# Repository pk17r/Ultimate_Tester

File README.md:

# Ultimate Tester!

Pocket Sized Component Tester + Variable Power Source + Accurate Power Monitor in Arduino Uno Form Factor

Full Blog Entry & Details:
https://pk17r.wordpress.com/2023/12/18/ultimate-tester-component-tester-lipo-charge-boost-protect/

Updated Ultimate Tester Schematics: https://github.com/pk17r/Ultimate_Tester/blob/prash/ComponentTester-1.54m/UltimateTester_PCB/UltimateTester_v1_with_mods.pdf

<br>

Current Accuracy:<br>
Test 1: Low Current: 2.4mA<br>
<table>
  <tr>
    <th></th>
    <th>Measured</th>
    <th>Ground Truth</th>
    <th>Error</th>
  </tr>
  <tr>
    <td>Current</td>
    <td>2.4mA</td>
    <td>2.39+0.6%=2.40mA</td>
    <td>0%</td>
  </tr>
  <tr>
    <td>Voltage</td>
    <td>5.17V</td>
    <td>5.164+0.1%=5.17V</td>
    <td>0%</td>
  </tr>
</table>

Test 2: Medium Current: 209.3mA<br>
<table>
  <tr>
    <th></th>
    <th>Measured</th>
    <th>Ground Truth</th>
    <th>Error</th>
  </tr>
  <tr>
    <td>Current</td>
    <td>209.3mA</td>
    <td>207.3+0.6%=208.5mA</td>
    <td>+0.4%</td>
  </tr>
  <tr>
    <td>Voltage</td>
    <td>5.14V</td>
    <td>5.135+0.1%=5.14V</td>
    <td>0%</td>
  </tr>
</table>

Test 3: High Current: 1.07A<br>
<table>
  <tr>
    <th></th>
    <th>Measured</th>
    <th>Ground Truth</th>
    <th>Error</th>
  </tr>
  <tr><td>Current</td><td>1.07mA</td><td>1.056+0.6%=1.06A</td><td>+0.9%</td></tr>
  <tr><td>Voltage</td><td>4.95V </td><td>4.928+0.1%=4.93V</td><td>+0.4%</td></tr>
</table>

Test 4: Different Voltages<br>
<table>
  <tr>
    <th>Measured</th>
    <th>Ground Truth</th>
    <th>Error</th>
  </tr>
  <tr><td>3.93V</td><td>  3.930+0.1%=3.93V</td><td>    0%</td></tr>
  <tr><td>9.05V</td><td>  9.051+0.1%=9.02V</td><td>   +0.3%</td></tr>
  <tr><td>12.04V</td><td>12.022+0.1%=12.03V</td><td>+0.1%</td></tr>
  <tr><td>15.15V</td><td>15.136+0.1%=15.15V</td><td>0%</td></tr>
</table>

<br>

# Transistortester Warehouse

The Transistortester is a device for identifying and checking electronic components.
It also offers additional functionality like a PWM signal generator for example.
And it's OSHW.

This repo is meant to provide a convenient way to download firmware packages,
documentation files, PCB files and more. Therefore it's structured differently
from the main repo.

The project's webpage is https://www.mikrocontroller.net/articles/AVR_Transistortester
and the main repo is https://github.com/kubi48/TransistorTester-source.

BTW, all the inexpensive Transistortesters sold on your favourite shopping platform
are based on this project and can be updated with the original OSHW firmware versions.

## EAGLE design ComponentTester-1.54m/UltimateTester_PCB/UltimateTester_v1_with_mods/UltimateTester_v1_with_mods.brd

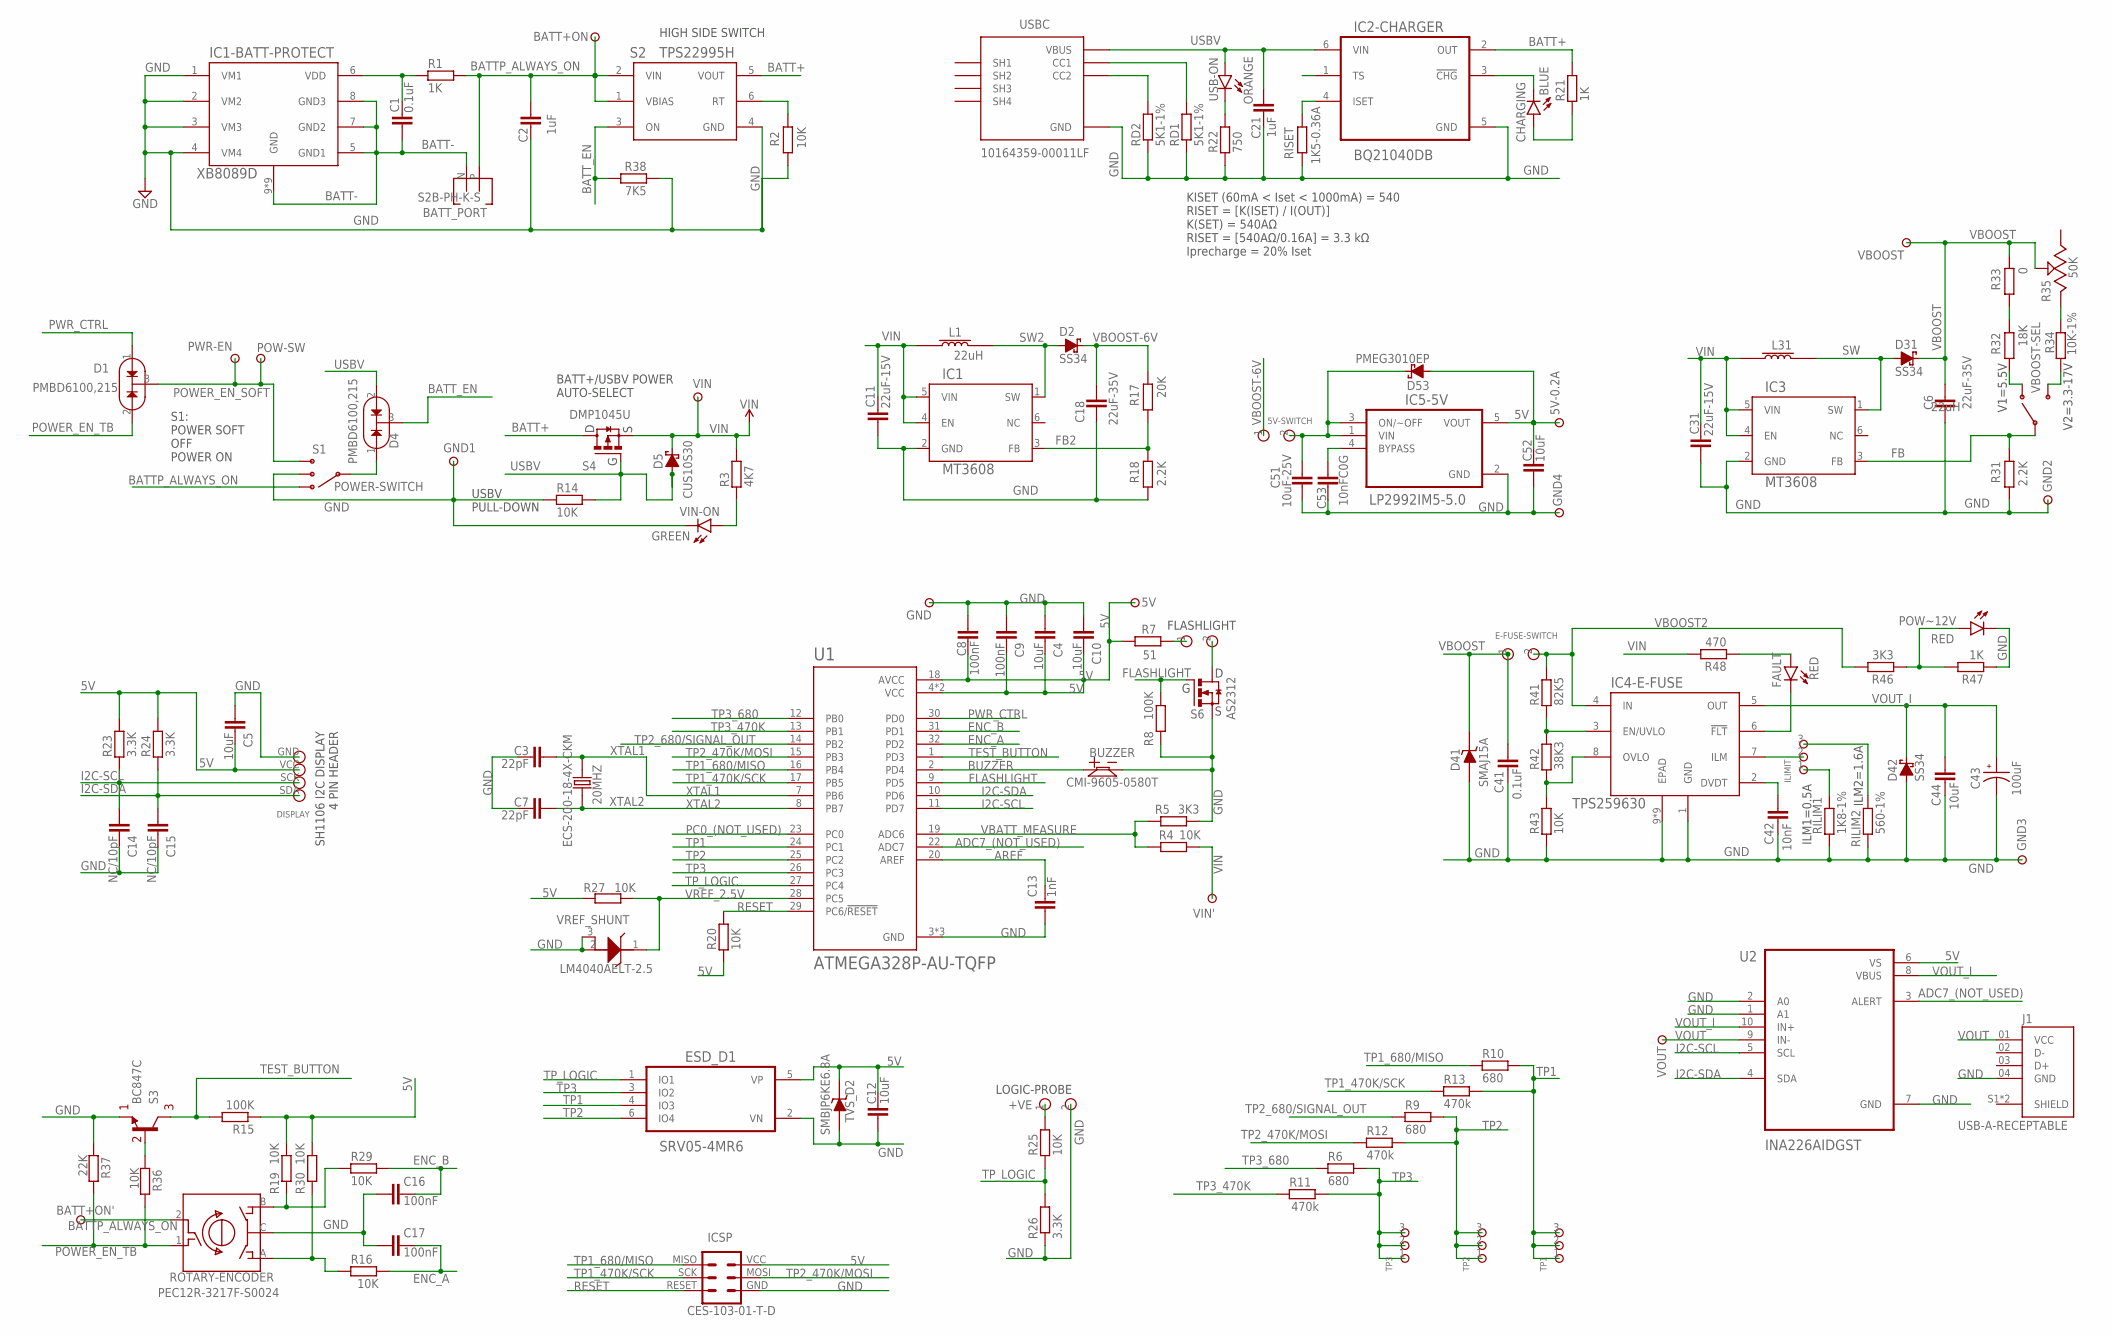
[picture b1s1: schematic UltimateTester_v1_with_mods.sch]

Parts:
5V, 5V-0.2A: TEST-POINT-TH; TEST-POINT-TH-1MM
5V-SWITCH: HEADER-2PIN-0.1"P
20MHZ: ECS-200-18-4X-CKM; XTAL_ECS-200-18-4X-CKM
BATT+ON: TEST-POINT-TH; TEST-POINT-TH-1MM
BATT+ON': TEST-POINT-TH; TEST-POINT-TH-1MM
BATT_PORT: S2B-PH-K-S
BUZZER: CMI-9605-0580T; BUZZER-ACTIVE-CMI-9605-0580T
C1, C41: 0.1uF; 0603
C2, C21: 1uF; 0603
C3, C7: 22pF; 0603
C4, C10, C12, C44, C52: 10uF; 0603
C5: 10uF; 1206
C6, C18: 22uF-35V; 1206
C8, C9, C16, C17: 100nF; 0603
C11, C31: 22uF-15V; 1206
C13: 1nF; 0603
C14, C15: NC/10pF; 0603
C42: 10nF; 0603
C43: 100uF; CAP_EEEFN1E101UP
C51: 10uF-25V; 0603
C53: 10nFC0G; 0603
CHARGING: BLUE; 0603-DIODE
D1, D4: PMBD6100,215; SOT-23-3
D2, D31, D42: SS34; SMA
D5: CUS10S30; SOD-323
D41: SMAJ15A; SMA
D53: PMEG3010EP; SOD-128
DISPLAY: DISPLAY-1.3"-SH1106-I2C
E-FUSE-SWITCH: HEADER-2PIN-0.1"P
ESD_D1: SRV05-4MR6; SOT-23-6
FAULT: RED; 0603-DIODE
FLASHLIGHT: HEADER-2PIN-0.2"P
GND, GND1, GND2, GND3, GND4: TEST-POINT-TH; TEST-POINT-TH-1MM
IC1, IC3: MT3608; SOT-23-6
IC1-BATT-PROTECT: XB8089D; SOIC-8-POWER-PAD
IC2-CHARGER: BQ21040DB; SOT-23-6
IC4-E-FUSE: TPS259630; SOIC-8-POWER-PAD
IC5-5V: LP2992IM5-5.0; SOT-23-5
ICSP: CES-103-01-T-D; HEADER-ICSP-0.1"P
ILIMIT: HEADER-3PIN-0.1"P
J1: USB-A-RECEPTABLE; AMPHENOL_87583-2010RLF
L1, L31: 22uH; INDUCTOR-SMRH74-220MT
LOGIC-PROBE: HEADER-2PIN-0.1"P
POW-SW: TEST-POINT-TH; TEST-POINT-TH-1MM
POW~12V: RED; 1206-DIODE
PWR-EN: TEST-POINT-TH; TEST-POINT-TH-1MM
R1, R21, R47: 1K; 0603
R2, R4, R14, R16, R19, R20, R25, R27, R29, R30, R36, R43: 10K; 0603
R3: 4K7; 0603
R5, R46: 3K3; 0603
R6, R9, R10: 680; 1206
R7: 51; 1206
R8, R15: 100K; 0603
R11, R12, R13: 470k; 1206
R17: 20K; 0603
R18, R31: 2.2K; 0603
R22: 750; 0603
R23, R24, R26: 3.3K; 0603
R32: 18K; 0603
R33: 0; 0603
R34: 10K-1%; 0603
R35: 50K; ROTARY-POTENTIOMETER-3386P
R37: 22K; 0603
R38: 7K5; 0603
R41: 82K5; 0603
R42: 38K3; 0603
R48: 470; 0603
RD1, RD2: 5K1-1%; 0603
RILIM1: 1K8-1%; 0603
RILIM2: 560-1%; 0603
RISET: 1K5-0.36A; 0603
ROTARY-ENCODER: PEC12R-3217F-S0024
S1: POWER-SWITCH; CSS-1310MC
S2: TPS22995H; SOT-23-6
S3: BC847C; SOT-23-3
S4: DMP1045U; SOT-23-3
S6: AS2312; SOT-23-3
TP1, TP2, TP3: HEADER-3PIN-0.1"P
TVS_D2: SMBJP6KE6.8A; DIOM5336X244N
U1: ATMEGA328P-AU-TQFP; TQFP32
U2: INA226AIDGST; SOP50P490X110-10N
USB-ON: ORANGE; 0603-DIODE
USBC: 10164359-00011LF; USB-C-RECEPTABLE-1016435900011LF
VBOOST: TEST-POINT-TH; TEST-POINT-TH-1MM
VBOOST-SEL: SLIDE-SWITCH-SPDT-VERTICLE-TH; SLW-883935-2A-D
VIN: TEST-POINT-TH; TEST-POINT-TH-1MM
VIN': TEST-POINT-TH; TEST-POINT-TH-1MM
VIN-ON: GREEN; 0603-DIODE
VOUT: TEST-POINT-TH; TEST-POINT-TH-1MM
VREF_SHUNT: LM4040AELT-2.5; SOT-23-3

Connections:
5V: 5V.P$1, 5V-0.2A.P$1, C4.1, C5.1, C8.2, C9.1, C10.1, C12.1, C52.2, D53.A, DISPLAY.VCC, ESD_D1.5 (VP), IC5-5V.5 (VOUT), ICSP.VCC (2), R7.1, R15.1, R19.2, R20.1, R23.2, R24.2, R27.1, R30.2, TVS_D2.C, U1.4 (VCC), U1.6 (VCC), U1.18 (AVCC), U2.6 (VS)
!FLT: FAULT.C, IC4-E-FUSE.6 (!FLT)
+VE: LOGIC-PROBE.1, R25.2
A: R16.1, R30.1, ROTARY-ENCODER.A
ADC7_(NOT_USED): U1.22 (ADC7), U2.3 (ALERT)
AREF: C13.1, U1.20 (AREF)
B: R19.1, R29.1, ROTARY-ENCODER.B
BATT+: IC2-CHARGER.2 (OUT), R21.2, S2.5 (VOUT), S4.3 (D)
BATT-: BATT_PORT.N, C1.2, IC1-BATT-PROTECT.5 (GND1), IC1-BATT-PROTECT.7 (GND2), IC1-BATT-PROTECT.8 (GND3), IC1-BATT-PROTECT.9 (GND), IC1-BATT-PROTECT.10 (GND), IC1-BATT-PROTECT.11 (GND), IC1-BATT-PROTECT.12 (GND), IC1-BATT-PROTECT.13 (GND), IC1-BATT-PROTECT.14 (GND), IC1-BATT-PROTECT.15 (GND), IC1-BATT-PROTECT.16 (GND), IC1-BATT-PROTECT.17 (GND)
BATTP_ALWAYS_ON: BATT+ON.P$1, BATT+ON'.P$1, BATT_PORT.P, C2.2, R1.2, ROTARY-ENCODER.2, S1.1, S2.1 (VBIAS), S2.2 (VIN)
BATT_EN: D4.3 (C), R38.2, S2.3 (ON)
BJT-B: R36.1, S3.1 (B)
BUZZER: BUZZER.P$1 (+), U1.2 (PD4)
BYP1: C53.2, IC5-5V.4 (BYPASS)
CHG: CHARGING.C, IC2-CHARGER.3 (!CHG)
DVDT: C42.2, IC4-E-FUSE.2 (DVDT)
EN/UVLO: IC4-E-FUSE.3 (EN/UVLO), R41.1, R42.2
ENC_A: C17.1, R16.2, U1.32 (PD2)
ENC_B: C16.1, R29.2, U1.31 (PD1)
FB: IC3.3 (FB), R31.1, VBOOST-SEL.C
FB2: IC1.3 (FB), R17.2, R18.1
FL+: FLASHLIGHT.1, R7.2
FL-: FLASHLIGHT.2, S6.3 (D)
FLASHLIGHT: R8.1, S6.1 (G), U1.9 (PD5)
GND: BUZZER.P$2 (-), C2.1, C3.1, C4.2, C5.2, C6.1, C7.1, C8.1, C9.2, C10.2, C11.1, C12.2, C13.2, C14.1, C15.1, C16.2, C17.2, C18.1, C21.1, C31.1, C41.1, C42.1, C43.2, C44.1, C51.1, C52.1, C53.1, D41.A, D42.A, DISPLAY.GND, ESD_D1.2 (VN), GND.P$1, GND1.P$1, GND2.P$1, GND3.P$1, GND4.P$1, IC1.2 (GND), IC1-BATT-PROTECT.1 (VM1), IC1-BATT-PROTECT.2 (VM2), IC1-BATT-PROTECT.3 (VM3), IC1-BATT-PROTECT.4 (VM4), IC2-CHARGER.5 (GND), IC3.2 (GND), IC4-E-FUSE.1 (GND), IC4-E-FUSE.9 (EPAD), IC4-E-FUSE.10 (EPAD), IC4-E-FUSE.11 (EPAD), IC4-E-FUSE.12 (EPAD), IC4-E-FUSE.13 (EPAD), IC4-E-FUSE.14 (EPAD), IC4-E-FUSE.15 (EPAD), IC4-E-FUSE.16 (EPAD), IC4-E-FUSE.17 (EPAD), IC5-5V.2 (GND), ICSP.GND (6), J1.04 (GND), LOGIC-PROBE.2, POW~12V.C1 (C), R2.2, R5.2, R8.2, R14.1, R18.2, R22.1, R26.1, R31.2, R37.1, R38.1, R43.1, R47.1, RD1.1, RD2.1, RILIM1.1, RILIM2.1, RISET.2, ROTARY-ENCODER.C, S1.2, S2.4 (GND), S3.2 (E), S6.2 (S), TVS_D2.A, U1.3 (GND), U1.5 (GND), U1.21 (GND), U2.1 (A1), U2.2 (A0), U2.7 (GND), USBC.A12 (GND), USBC.B12 (GND), VIN-ON.C, VREF_SHUNT.2 (A), VREF_SHUNT.3 (NC/A)
I2C-SCL: C14.2, DISPLAY.SCK, R23.1, U1.11 (PD7), U2.5 (SCL)
I2C-SDA: C15.2, DISPLAY.SDA, R24.1, U1.10 (PD6), U2.4 (SDA)
ILM: IC4-E-FUSE.7 (ILM), ILIMIT.2
ILM1: ILIMIT.1, RILIM1.2
ILM2: ILIMIT.3, RILIM2.2
ISET: IC2-CHARGER.4 (ISET), RISET.1
unnamed: RD2.2, USBC.B5 (CC2)
unnamed: RD1.2, USBC.A5 (CC1)
unnamed: R22.2, USB-ON.C
unnamed: R32.2, VBOOST-SEL.1
unnamed: R3.1, VIN-ON.A
unnamed: FAULT.A, R48.1
unnamed: CHARGING.A, R21.1
unnamed: R32.1, R33.2
unnamed: R34.2, VBOOST-SEL.2
unnamed: POW~12V.A1 (A), R46.1, R47.2
unnamed: R34.1, R35.3 (CCW)
OVLO: IC4-E-FUSE.8 (OVLO), R42.1, R43.2
PC0_(NOT_USED): U1.23 (PC0)
POWER_EN_SOFT: D1.3 (C), POW-SW.P$1, PWR-EN.P$1, S1.3
POWER_EN_TB: D1.2 (A2), R36.2, R37.2, ROTARY-ENCODER.1
PWR_CTRL: D1.1 (A1), U1.30 (PD0)
PWR_SW: D4.1 (A1), S1.C
RESET: ICSP.RESET (5), R20.2, U1.29 (PC6/!RESET)
RT: R2.1, S2.6 (RT)
SW: D31.A, IC3.1 (SW), L31.P$2
SW2: D2.A, IC1.1 (SW), L1.P$2
TEST_BUTTON: R15.2, S3.3 (C), U1.1 (PD3)
TP1: ESD_D1.4 (IO3), R10.2, R13.2, TP1.1, TP1.2, TP1.3, U1.24 (PC1)
TP1_470K/SCK: ICSP.SCK (3), R13.1, U1.17 (PB5)
TP1_680/MISO: ICSP.MISO (1), R10.1, U1.16 (PB4)
TP2: ESD_D1.6 (IO4), R9.2, R12.2, TP2.1, TP2.2, TP2.3, U1.25 (PC2)
TP2_470K/MOSI: ICSP.MOSI (4), R12.1, U1.15 (PB3)
TP2_680/SIGNAL_OUT: R9.1, U1.14 (PB2)
TP3: ESD_D1.3 (IO2), R6.2, R11.2, TP3.1, TP3.2, TP3.3, U1.26 (PC3)
TP3_470K: R11.1, U1.13 (PB1)
TP3_680: R6.1, U1.12 (PB0)
TP_LOGIC: ESD_D1.1 (IO1), R25.1, R26.2, U1.27 (PC4)
TS: IC2-CHARGER.1 (TS)
USBV: C21.2, D4.2 (A2), D5.A, IC2-CHARGER.6 (VIN), R14.2, S4.1 (G), USB-ON.A, USBC.A9 (VBUS), USBC.B9 (VBUS)
VBATT_MEASURE: R4.2, R5.1, U1.19 (ADC6)
VBOOST: C6.2, C41.2, D31.C, D41.C, E-FUSE-SWITCH.1, R33.1, R35.2 (S), VBOOST.P$1
VBOOST2: E-FUSE-SWITCH.2, IC4-E-FUSE.4 (IN), R41.2, R46.2
VBOOST-6V: 5V-SWITCH.1, C18.2, D2.C, R17.1
VBOOST-6V-: 5V-SWITCH.2, C51.2, D53.K (C), IC5-5V.1 (VIN), IC5-5V.3 (ON/~OFF)
VDD: C1.1, IC1-BATT-PROTECT.6 (VDD), R1.1
VIN: C11.2, C31.2, D5.C, IC1.4 (EN), IC1.5 (VIN), IC3.4 (EN), IC3.5 (VIN), L1.P$1, L31.P$1, R3.2, R4.1, R48.2, S4.2 (S), VIN.P$1, VIN'.P$1
VOUT: J1.01 (VCC), U2.9 (IN-), VOUT.P$1
VOUT_I: C43.1, C44.2, D42.C, IC4-E-FUSE.5 (OUT), U2.8 (VBUS), U2.10 (IN+)
VREF_2.5V: R27.2, U1.28 (PC5), VREF_SHUNT.1 (C)
XTAL1: 20MHZ.2, C3.2, U1.7 (PB6)
XTAL2: 20MHZ.1, C7.2, U1.8 (PB7)

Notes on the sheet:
HIGH SIDE SWITCH
KISET (60mA < Iset < 1000mA) = 540 RISET = [K(ISET) / I(OUT)] K(SET) = 540AΩ RISET = [540AΩ/0.16A] = 3.3 kΩ Iprecharge = 20% Iset
BATT+/USBV POWER AUTO-SELECT
USBV PULL-DOWN
S1: POWER SOFT OFF POWER ON
V1=5.5V
V2=3.3-17V
ILM2=1.6A
ILM1=0.5A

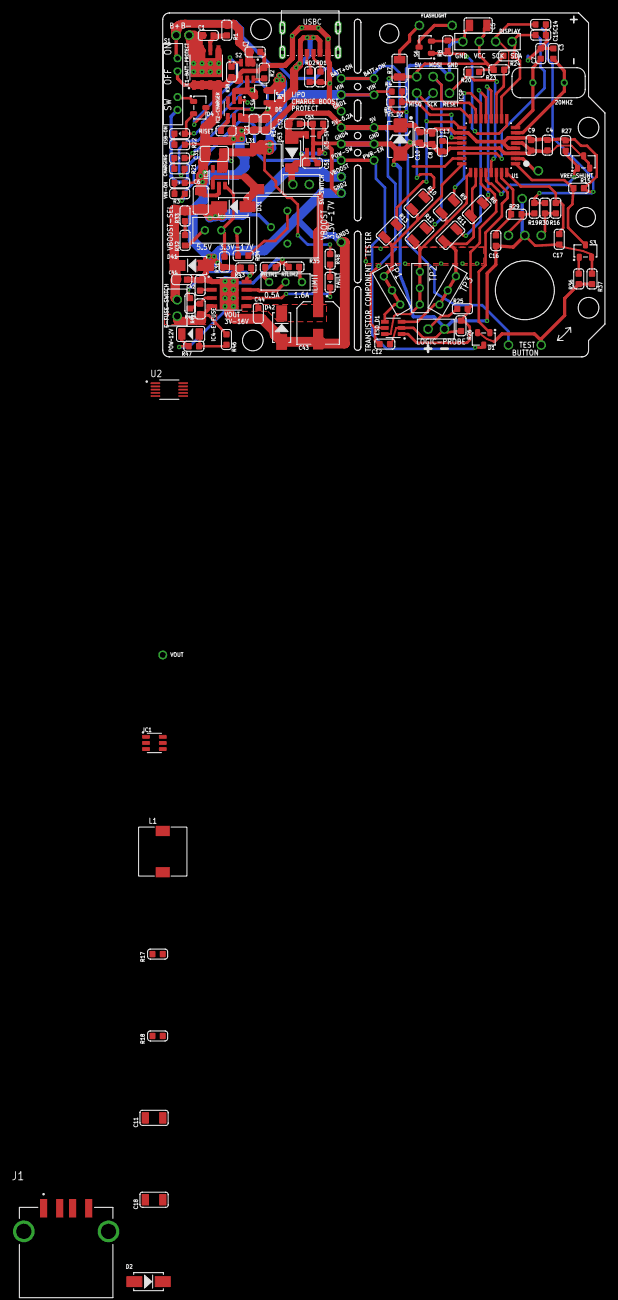
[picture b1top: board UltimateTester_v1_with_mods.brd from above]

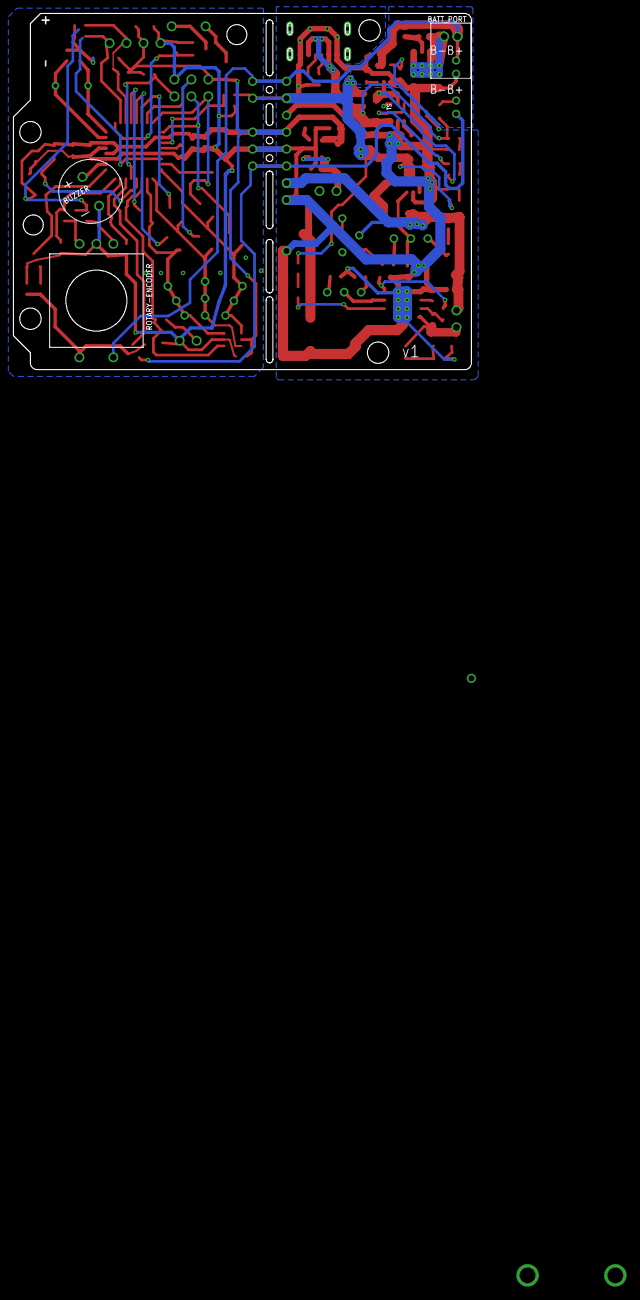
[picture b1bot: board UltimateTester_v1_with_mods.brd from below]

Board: 2 copper layers, 68.6 x 53.3 mm, 138 parts (2 on the bottom side), 75 nets.

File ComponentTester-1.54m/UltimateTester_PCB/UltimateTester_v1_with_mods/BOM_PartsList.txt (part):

Partlist

Exported from LiBatteryChargeBoostBoard.sch at 17-Dec-23 11:04 PM

EAGLE Version 9.6.2 Copyright (c) 1988-2020 Autodesk, Inc.

Assembly variant: 

Part             Value              Device                                   Package                          Library       Sheet

5V               TEST-POINT-TH      TEST-POINT-TH                            TEST-POINT-TH-1MM                .MyComponents 1
5V-0.2A          TEST-POINT-TH      TEST-POINT-TH                            TEST-POINT-TH-1MM                .MyComponents 1
5V-SWITCH                           HEADER-2PIN-0.1"P                        HEADER-2PIN-0.1"P                .MyComponents 1
20MHZ            ECS-200-18-4X-CKM  CRYSTAL-20MHZ-ECS-200-18-4X-CKM          XTAL_ECS-200-18-4X-CKM           .MyComponents 1
BATT+ON          TEST-POINT-TH      TEST-POINT-TH                            TEST-POINT-TH-1MM                .MyComponents 1
BATT+ON'         TEST-POINT-TH      TEST-POINT-TH                            TEST-POINT-TH-1MM                .MyComponents 1
BATT_PORT        S2B-PH-K-S         S2B-PH-K-S                               S2B-PH-K-S                       .MyComponents 1
BUZZER           CMI-9605-0580T     BUZZER-ACTIVE-CMI-9605-0580T             BUZZER-ACTIVE-CMI-9605-0580T     .MyComponents 1
C1               0.1uF              CAPACITOR_SMD0603                        0603                             .MyComponents 1
C2               1uF                CAPACITOR_SMD0603                        0603                             .MyComponents 1
C3               22pF               CAPACITOR_SMD0603                        0603                             .MyComponents 1
C4               10uF               CAPACITOR_SMD0603                        0603                             .MyComponents 1
C5               10uF               CAPACITOR1206                            1206                             .MyComponents 1
C6               22uF-35V           CAPACITOR_SMD1206                        1206                             .MyComponents 1
C7               22pF               CAPACITOR_SMD0603                        0603                             .MyComponents 1
C8               100nF              CAPACITOR_SMD0603                        0603                             .MyComponents 1
C9               100nF              CAPACITOR_SMD0603                        0603                             .MyComponents 1
C10              10uF               CAPACITOR_SMD0603                        0603                             .MyComponents 1
C12              10uF               CAPACITOR_SMD0603                        0603                             .MyComponents 1
C13              1nF                CAPACITOR_SMD0603                        0603                             .MyComponents 1
C14              NC/10pF            CAPACITOR_SMD0603                        0603                             .MyComponents 1
C15              NC/10pF            CAPACITOR_SMD0603                        0603                             .MyComponents 1
C16              100nF              CAPACITOR_SMD0603                        0603                             .MyComponents 1
C17              100nF              CAPACITOR_SMD0603                        0603                             .MyComponents 1
C21              1uF                CAPACITOR_SMD0603                        0603                             .MyComponents 1
C31              22uF-15V           CAPACITOR_SMD1206                        1206                             .MyComponents 1
C41              0.1uF              CAPACITOR_SMD0603                        0603                             .MyComponents 1
C42              10nF               CAPACITOR_SMD0603                        0603                             .MyComponents 1
C43              100uF              EEEFN1E101UP                             CAP_EEEFN1E101UP                 .MyComponents 1
C44              10uF               CAPACITOR_SMD0603                        0603                             .MyComponents 1
C51              10uF-25V           CAPACITOR0603                            0603                             .MyComponents 1
C52              10uF               CAPACITOR0603                            0603                             .MyComponents 1
C53              10nFC0G            CAPACITOR_SMD0603                        0603                             .MyComponents 1
CHARGING         BLUE               LED0603                                  0603-DIODE                       .MyComponents 1
D1               PMBD6100           DIODE-DOUBLE-COMMON-CATHODE-PMBD6100,215 SOT-23-3                         .MyComponents 1
D4               PMBD6100           DIODE-DOUBLE-COMMON-CATHODE-PMBD6100,215 SOT-23-3                         .MyComponents 1
D5               CUS10S30           DIODE-SCHOTTKY-CUS10S30,H3F              SOD-323                          .MyComponents 1
D31              SS34               DIODE-SCHOTTKY-SS34                      SMA                              .MyComponents 1
D41              SMAJ15A            DIODE-TVS-SMA                            SMA                              .MyComponents 1
D42              SS34               DIODE-SCHOTTKY-SS34                      SMA                              .MyComponents 1
D53              PMEG3010EP         DIODE-SCHOTTKY-PMEG3010EP,115            SOD-128                          .MyComponents 1
DISPLAY                             DISPLAY-1.3"-SH1106-I2C                  DISPLAY-1.3"-SH1106-I2C          .MyComponents 1
E-FUSE-SWITCH                       HEADER-2PIN-0.1"P                        HEADER-2PIN-0.1"P                .MyComponents 1
ESD_D1           SRV05-4MR6         SRV05-4MR6T1G                            SOT-23-6                         .MyComponents 1
FAULT            RED                LED0603                                  0603-DIODE                       .MyComponents 1
FLASHLIGHT       HEADER-2PIN-0.2"P  HEADER-2PIN-0.2"P                        HEADER-2PIN-0.2"P                .MyComponents 1
GND              TEST-POINT-TH      TEST-POINT-TH                            TEST-POINT-TH-1MM                .MyComponents 1
GND1             TEST-POINT-TH      TEST-POINT-TH                            TEST-POINT-TH-1MM                .MyComponents 1
GND2             TEST-POINT-TH      TEST-POINT-TH                            TEST-POINT-TH-1MM                .MyComponents 1
GND3             TEST-POINT-TH      TEST-POINT-TH                            TEST-POINT-TH-1MM                .MyComponents 1
GND4             TEST-POINT-TH      TEST-POINT-TH                            TEST-POINT-TH-1MM                .MyComponents 1
I-SENSE-HEADER   CES-102-02-G-S-RA  HEADER-2PIN-0.1"P                        HEADER-2PIN-0.1"P                .MyComponents 1
IC1-BATT-PROTECT XB8089D            XB8089D                                  SOIC-8-POWER-PAD                 .MyComponents 1
IC2-CHARGER      BQ21040DB          BQ21040DBVR                              SOT-23-6                         .MyComponents 1
IC3              MT3608             MT3608                                   SOT-23-6                         .MyComponents 1
IC4-E-FUSE       TPS259630          TPS259621DDAR                            SOIC-8-POWER-PAD                 .MyComponents 1
IC5-5V           LP2992IM5-5.0      LP2992IM5-5.0                            SOT-23-5                         .MyComponents 1
IC6-I-SENSE      TMCS1108A4B        TMCS1108A4B-CURRENT-SENSE                SOIC-8                           .MyComponents 1
ICSP             CES-103-01-T-D     HEADER-ICSP-0.1"P                        HEADER-ICSP-0.1"P                .MyComponents 1
ILIMIT                              HEADER-3PIN-0.1"P                        HEADER-3PIN-0.1"P                .MyComponents 1
L31              22uH               INDUCTOR-SMRH74-220MT                    INDUCTOR-SMRH74-220MT            .MyComponents 1
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
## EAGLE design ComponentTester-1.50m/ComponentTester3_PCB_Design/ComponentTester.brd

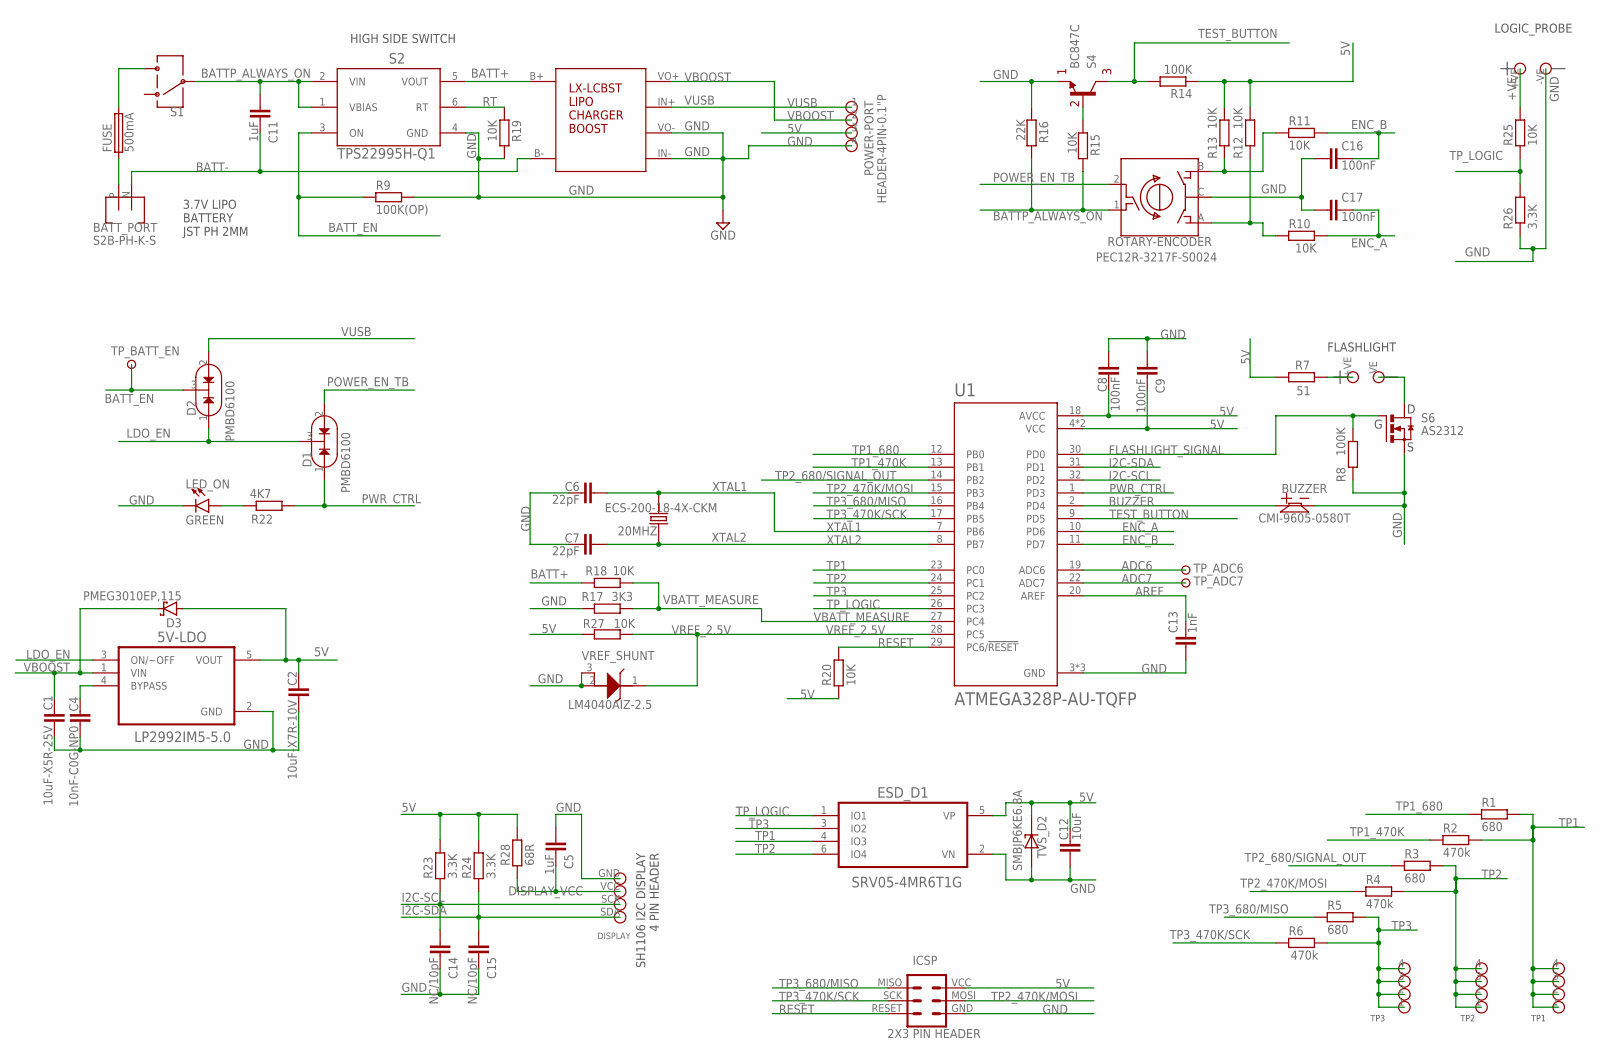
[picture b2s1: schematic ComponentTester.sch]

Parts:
5V-LDO: LP2992IM5-5.0; SOT-23-5
20MHZ: ECS-200-18-4X-CKM; XTAL_ECS-200-18-4X-CKM
BATT_PORT: S2B-PH-K-S
BUZZER: CMI-9605-0580T; BUZZER-ACTIVE-CMI-9605-0580T
C1: 10uF-X5R-25V; 0603
C2: 10uF-X7R-10V; 0603
C4: 10nF-C0G-NP0; 0603
C5, C11: 1uF; 0603
C6, C7: 22pF; 0603
C8, C9, C16, C17: 100nF; 0603
C12: 10uF; 0603
C13: 1nF; 0603
C14, C15: NC/10pF; 0603
CHARGE_BOOST: BATTERY-CHARGER-BOOST-MODULE-LX-LCBST
D1, D2: PMBD6100; SOT-23-3
D3: PMEG3010EP,115; SOD-128
DISPLAY: DISPLAY-1.3"-SH1106-I2C
ESD_D1: SRV05-4MR6T1G; SOT-23-6
FLASHLIGHT: HEADER-2PIN-0.2"P
FUSE: 500mA; 1206
ICSP: 2X3 PIN HEADER; HEADER-ICSP-0.1"P
LED_ON: GREEN; 1206-DIODE
LOGIC_PROBE: HEADER-2PIN-0.2"P-LOGIC-PROBE
POWER-PORT: HEADER-4PIN-0.1"P
R1, R3, R5: 680; 1206
R2, R4, R6: 470k; 1206
R7: 51; 1206
R8, R14: 100K; 0603
R9: 100K(OP); 0603
R10, R11, R12, R13, R15, R18, R19, R20, R25, R27: 10K; 0603
R16: 22K; 0603
R17: 3K3; 0603
R22: 4K7; 0603
R23, R24, R26: 3.3K; 0603
R28: 68R; 0603
ROTARY-ENCODER: PEC12R-3217F-S0024
S1: SLW-913535-2A-RA-D
S2: TPS22995H-Q1; SOT-23-6
S4: BC847C; SOT-23-3
S6: AS2312; SOT-23-3
TP1, TP2, TP3: HEADER-4PIN-0.1"P
TP_ADC6, TP_ADC7: TEST-POINT-TH; TEST-POINT-TH-1MM
TP_BATT_EN: TEST-POINT-SMD; TEST-POINT-SMD-1MM
TVS_D2: SMBJP6KE6.8A; DIOM5336X244N
U1: ATMEGA328P-AU-TQFP; TQFP32
VREF_SHUNT: LM4040AIZ-2.5; SOT-23-3

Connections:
5V: 5V-LDO.5 (VOUT), C2.2, C8.2, C9.1, C12.1, D3.A, ESD_D1.5 (VP), ICSP.VCC (2), POWER-PORT.3, R7.1, R12.2, R13.2, R14.1, R20.1, R23.2, R24.2, R27.1, R28.2, TVS_D2.C, U1.4 (VCC), U1.6 (VCC), U1.18 (AVCC)
+VE: LOGIC_PROBE.+VE, R25.2
ADC6: TP_ADC6.P$1, U1.19 (ADC6)
ADC7: TP_ADC7.P$1, U1.22 (ADC7)
AREF: C13.1, U1.20 (AREF)
BATT+: CHARGE_BOOST.B+, R18.2, S2.5 (VOUT)
BATT+_PORT: BATT_PORT.P, FUSE.1
BATT-: BATT_PORT.N, C11.1, CHARGE_BOOST.B-
BATTP_ALWAYS_ON: C11.2, ROTARY-ENCODER.2, S1.2, S2.1 (VBIAS), S2.2 (VIN)
BATT_EN: D2.3 (C), R9.1, S2.3 (ON), TP_BATT_EN.P$1
BUZZER: BUZZER.P$1, U1.2 (PD4)
BYP: 5V-LDO.4 (BYPASS), C4.2
DISPLAY_VCC: C5.1, DISPLAY.VCC, R28.1
ENC_A: C17.1, R10.2, U1.10 (PD6)
ENC_B: C16.1, R11.2, U1.11 (PD7)
FLASHLIGHT_SIGNAL: R8.1, S6.1 (G), U1.30 (PD0)
FUSE_2_SWITCH: FUSE.2, S1.3
GND: 5V-LDO.2 (GND), BUZZER.P$2, C1.1, C2.1, C4.1, C5.2, C6.1, C7.1, C8.1, C9.2, C12.2, C13.2, C14.1, C15.1, C16.2, C17.2, CHARGE_BOOST.IN- (USB-), CHARGE_BOOST.VO-, DISPLAY.GND, ESD_D1.2 (VN), ICSP.GND (6), LED_ON.C, LOGIC_PROBE.-VE, POWER-PORT.4, R8.2, R9.2, R16.1, R17.1, R19.2, R26.1, ROTARY-ENCODER.C, S2.4 (GND), S4.2 (E), S6.2 (S), TVS_D2.A, U1.3 (GND), U1.5 (GND), U1.21 (GND), VREF_SHUNT.2 (A), VREF_SHUNT.3 (NC/A)
I2C-SCL: C14.2, DISPLAY.SCK, R23.1, U1.32 (PD2)
I2C-SDA: C15.2, DISPLAY.SDA, R24.1, U1.31 (PD1)
LDO_EN: 5V-LDO.3 (ON/~OFF), D1.3 (C), D2.1 (A1)
unnamed: R11.1, R13.1, ROTARY-ENCODER.B
unnamed: FLASHLIGHT.-VE, S6.3 (D)
unnamed: R10.1, R12.1, ROTARY-ENCODER.A
unnamed: R15.1, S4.1 (B)
unnamed: FLASHLIGHT.+VE, R7.2
POWER_EN_TB: D1.2 (A2), R15.2, R16.2, ROTARY-ENCODER.1
PWR_CTRL: D1.1 (A1), R22.2, U1.1 (PD3)
RESET: ICSP.RESET (5), R20.2, U1.29 (PC6/!RESET)
RT: R19.1, S2.6 (RT)
TEST_BUTTON: R14.2, S4.3 (C), U1.9 (PD5)
TO_LED: LED_ON.A, R22.1
TP1: ESD_D1.4 (IO3), R1.2, R2.2, TP1.1, TP1.2, TP1.3, TP1.4, U1.23 (PC0)
TP1_470K: R2.1, U1.13 (PB1)
TP1_680: R1.1, U1.12 (PB0)
TP2: ESD_D1.6 (IO4), R3.2, R4.2, TP2.1, TP2.2, TP2.3, TP2.4, U1.24 (PC1)
TP2_470K/MOSI: ICSP.MOSI (4), R4.1, U1.15 (PB3)
TP2_680/SIGNAL_OUT: R3.1, U1.14 (PB2)
TP3: ESD_D1.3 (IO2), R5.2, R6.2, TP3.1, TP3.2, TP3.3, TP3.4, U1.25 (PC2)
TP3_470K/SCK: ICSP.SCK (3), R6.1, U1.17 (PB5)
TP3_680/MISO: ICSP.MISO (1), R5.1, U1.16 (PB4)
TP_LOGIC: ESD_D1.1 (IO1), R25.1, R26.2, U1.26 (PC3)
VBATT_MEASURE: R17.2, R18.1, U1.27 (PC4)
VBOOST: 5V-LDO.1 (VIN), C1.2, CHARGE_BOOST.VO+, D3.K (C), POWER-PORT.2
VREF_2.5V: R27.2, U1.28 (PC5), VREF_SHUNT.1 (C)
VUSB: CHARGE_BOOST.IN+ (USB+), D2.2 (A2), POWER-PORT.1
XTAL1: 20MHZ.2, C6.2, U1.7 (PB6)
XTAL2: 20MHZ.1, C7.2, U1.8 (PB7)

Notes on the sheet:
3.7V LIPO BATTERY JST PH 2MM
HIGH SIDE SWITCH

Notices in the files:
ComponentTester-1.50m_ATmega1284p_ArduinoIDE/Files/config_644.h:
(c) 2012-2023 by Markus Reschke
parts and their libraries:
COPYRIGHT: Copyright (C) 2023 Ultra Librarian. All rights reserved.
SparkFun-PowerSymbols: Licensing: Creative Commons ShareAlike 4.0 International - https://creativecommons.org/licenses/by-sa/4.0
